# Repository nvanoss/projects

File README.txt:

Updated 07/21/2020                                                                                 |

Hello and welcome to my repository!

SENIOR DESIGN PROJECT: My senior design project was a miniature robot that swims using surface
	acoustic wave streaming. The final pitch slides and poster are given in this directory,
	while Inventor and MATLAB files are stored in the appropriately named directories. My
	primary responsibility for the project was optimizing the SAW streaming, which encompassed
	designing and manufacturing the Interdigital Transducers and 3D printed structure. 

INVENTOR: this directory contains the AutoDesk Inventor files I used to design, manufacture, and
	present the 3D printed structure of the bot.

MATLAB: this directory contains code that was used for my senior design project and faculty
	research. Look inside for a more detailed README.

LABVIEW: this directory contains code that was used to automate electro-polling experiments for
	simulating neuro-plasmonic signal detection and microfluidic experiments for detecting
	HIV and other pathogens. Look inside for a more detailed README.

PCB/Distributed_Crosstalk_Project: For the final project of my High-Speed Digital Design class, I
	designed a custom experiment on an FR-4 printed circuit board that investigates the effects
	of distributed crosstalk on digital signals.

plant.oss.v1.0: this directory contains images and design files for my custom household automation
	circuit board on a compact footprint using a PIC12 MCU with a header pins for rapid firmware
	prototyping, dual SSR control, a potentiometer dial for user input, and free I/O headers for
	modular builds.

PSIM: this directory contains simulations of some power conversion systems I investigated as part of
	my power electronics class.

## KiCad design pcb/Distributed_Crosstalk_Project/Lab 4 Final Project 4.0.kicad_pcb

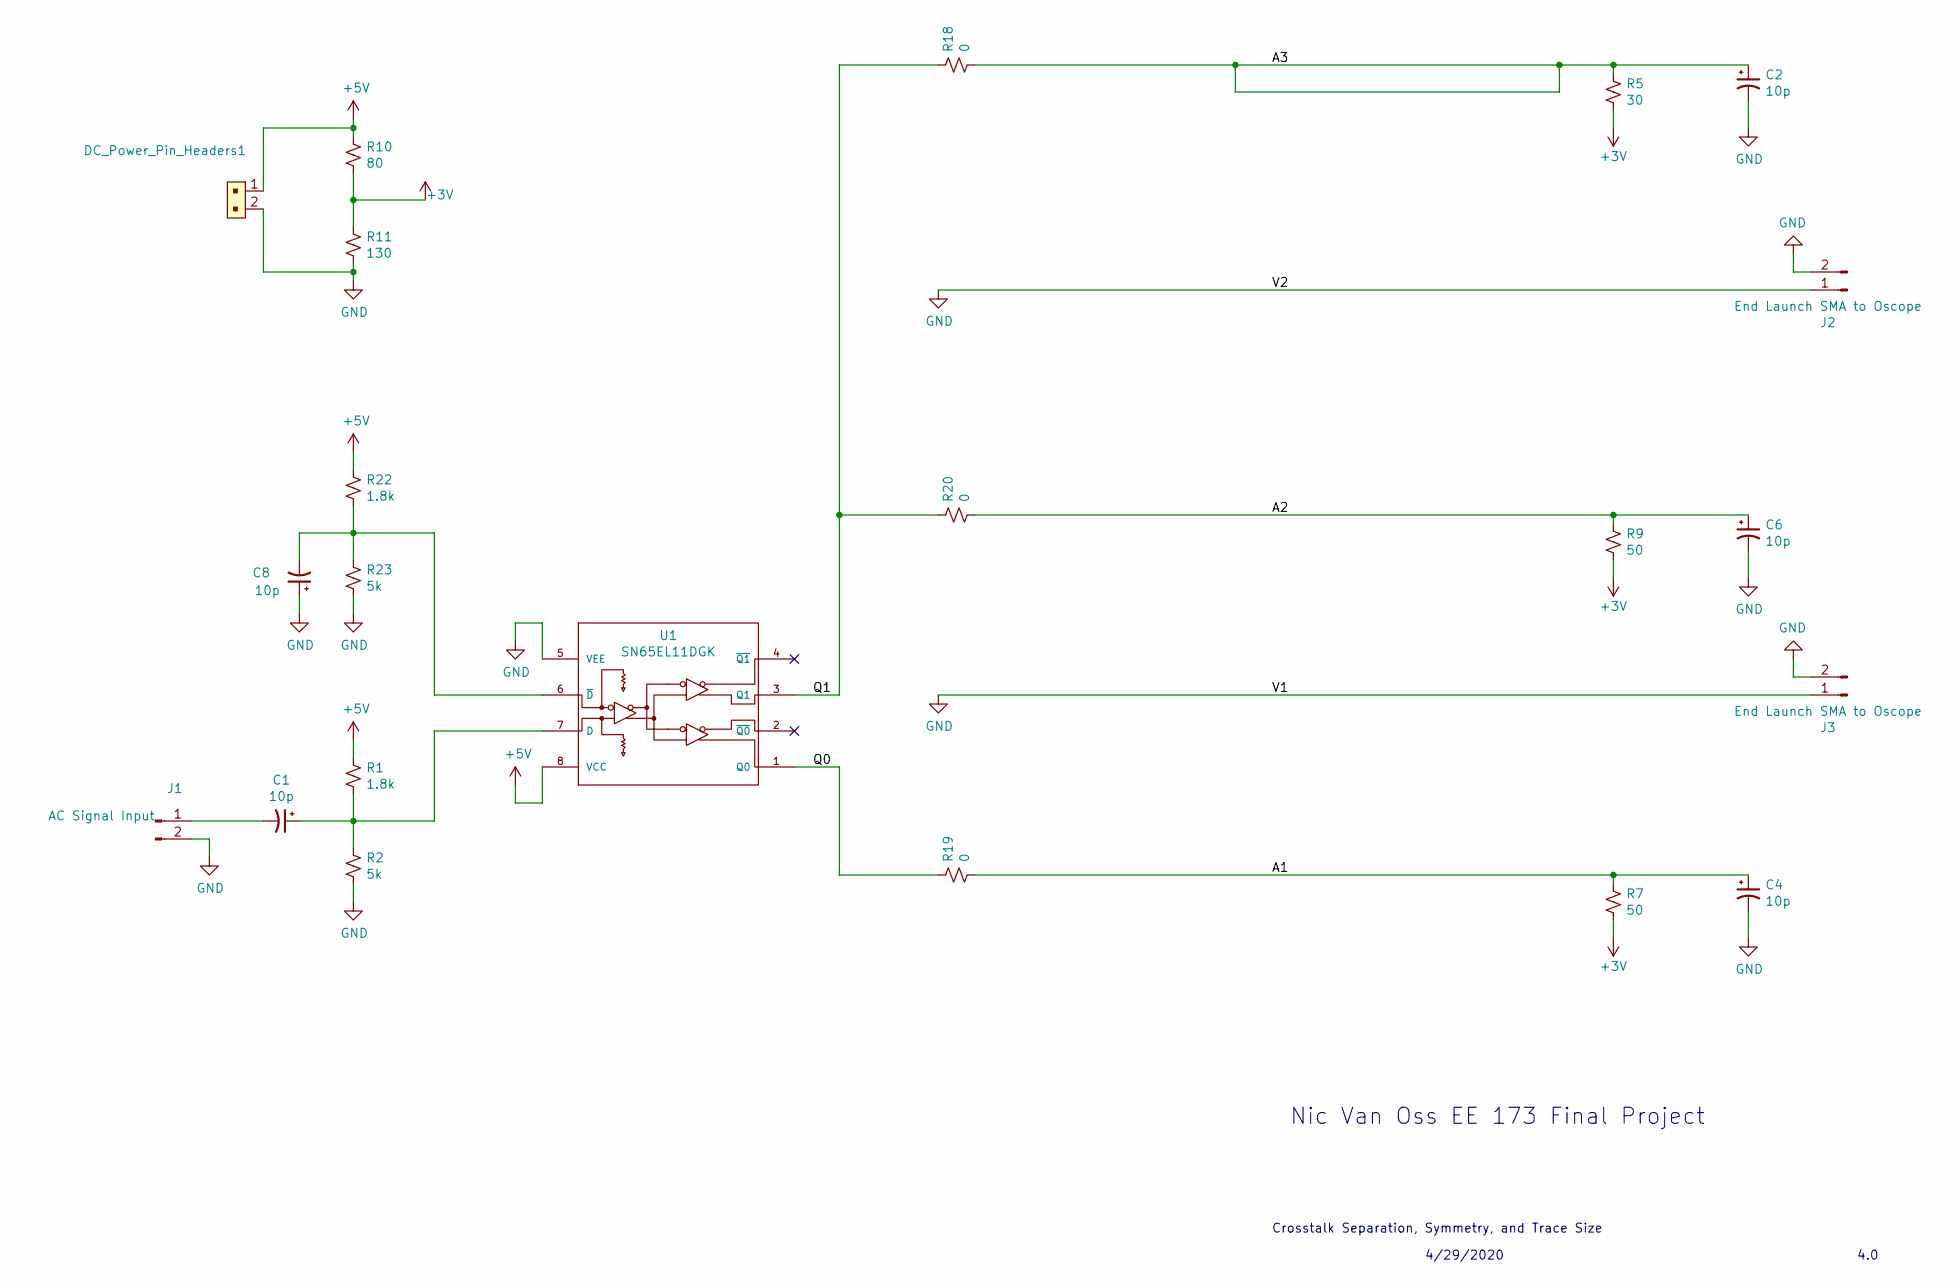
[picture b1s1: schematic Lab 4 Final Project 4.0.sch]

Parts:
C1, C2, C4, C6, C8: 10p; C_0805_2012Metric_Pad1.15x1.40mm_HandSolder
DC_Power_Pin_Headers1: 22-23-2021; PinHeader_1x2_P2.54mm_Drill1.02mm; MPN 22-23-2021; Digi-Key_PN WM4200-ND
J1: Conn_01x02_Male; SMA_Molex_73251-1153_EdgeMount_Horizontal
J2, J3: End Launch SMA to Oscope; SMA_Molex_73251-1153_EdgeMount_Horizontal
R1, R22: 1.8k; R_0805_2012Metric_Pad1.15x1.40mm_HandSolder
R2, R23: 5k; R_0805_2012Metric_Pad1.15x1.40mm_HandSolder
R5: 30; R_0805_2012Metric_Pad1.15x1.40mm_HandSolder
R7, R9: 50; R_0805_2012Metric_Pad1.15x1.40mm_HandSolder
R10: 80; R_0805_2012Metric_Pad1.15x1.40mm_HandSolder
R11: 130; R_0805_2012Metric_Pad1.15x1.40mm_HandSolder
R18, R19, R20: 0; R_0805_2012Metric_Pad1.15x1.40mm_HandSolder
U1: SN65EL11DGK; SOP65P490X110-8N

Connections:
+2V5: R5.2, R7.2, R9.2, R10.2, R11.1
+5V: DC_Power_Pin_Headers1.1, R1.1, R10.1, R22.1, U1.8 (VCC); also elsewhere on the board
/A1: C4.1, R7.1, R19.2
/A2: C6.1, R9.1, R20.2
/A3: C2.1, R5.1, R18.2
/Q0: R19.1, U1.1 (Q0)
/Q1: R18.1, R20.1, U1.3 (Q1)
GND: C2.2, C4.2, C6.2, C8.1, DC_Power_Pin_Headers1.2, J1.2, J2.1, J2.2, J3.1, J3.2, R2.2, R11.2, R23.2, U1.5 (VEE); also elsewhere on the board
unnamed: C1.1, R1.2, R2.1, U1.7 (D)
unnamed: C1.2, J1.1
unnamed: C8.2, R22.2, R23.1, U1.6 (~D)

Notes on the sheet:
Nic Van Oss EE 173 Final Project
Crosstalk Separation, Symmetry, and Trace Size
4/29/2020
4.0

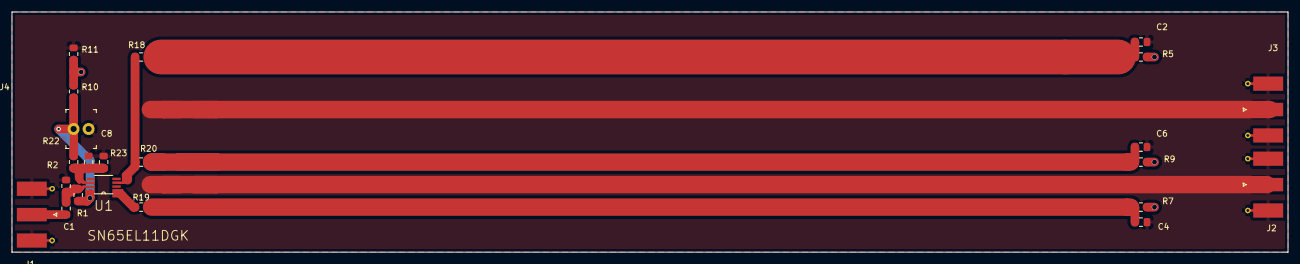
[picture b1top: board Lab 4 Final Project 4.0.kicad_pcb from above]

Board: 2 copper layers, 215.9 x 40.6 mm, 22 parts (0 on the bottom side), 11 nets.

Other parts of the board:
J4: DC Power Pin Headers; PinHeader_1x2_P2.54mm_Drill1.02mm

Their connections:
+5V: J4.1; also elsewhere on the board
GND: J4.2; also elsewhere on the board

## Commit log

2020-07-20 directory structure
2020-07-20 cleanup
2020-07-20 inventor
2020-07-20 power electronics
2020-07-21 senior design project
2020-07-21 README
2020-07-21 spellcheck
2026-05-01 plant.oss.v1.0
